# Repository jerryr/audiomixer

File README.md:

# audiomixer
Kicad project for audio mixer

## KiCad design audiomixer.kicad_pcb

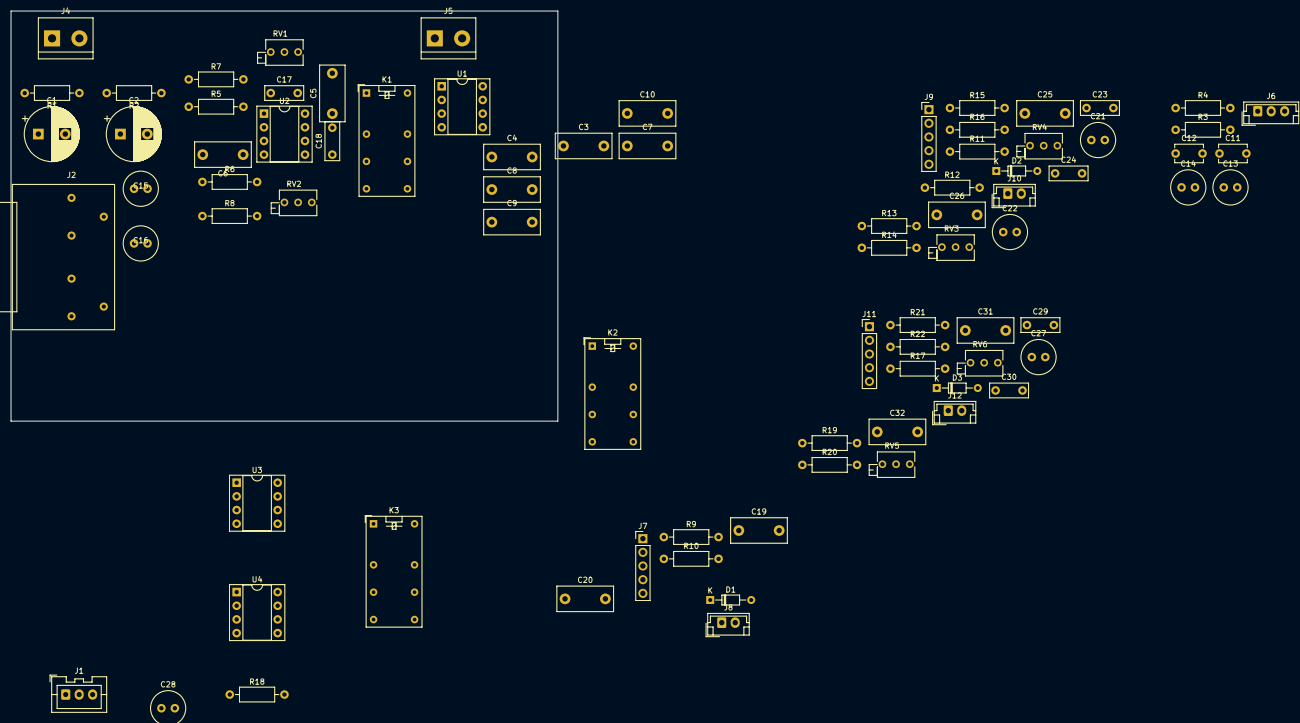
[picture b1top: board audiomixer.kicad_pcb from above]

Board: 2 copper layers, 101.6 x 76.2 mm, 81 parts (0 on the bottom side), 62 nets, no tracks yet.

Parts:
C1, C2: 1000uF; CP_Radial_D10.0mm_P5.00mm
C3, C4, C5, C6, C7, C8, C9, C10: 100n; C_Rect_L10.3mm_W4.5mm_P7.50mm_MKS4
C11, C12: 22p; C_Disc_D5.1mm_W3.2mm_P5.00mm
C13, C14: 22u; C_Radial_D6.3mm_H11.0mm_P2.50mm
C15, C16, C21, C22, C27, C28: 10u; C_Radial_D6.3mm_H11.0mm_P2.50mm
C17, C18, C23, C24, C29, C30: 47p; C_Rect_L7.0mm_W2.5mm_P5.00mm
C19, C20, C25, C26, C31, C32: 10u; C_Rect_L10.3mm_W4.5mm_P7.50mm_MKS4
D1, D2, D3: DIODE; D_DO-34_SOD68_P7.62mm_Horizontal
J1: Channel 3 In; JST_XA_B03B-XASK-1_1x03_P2.50mm_Vertical
J2: Dual_Stereo_RCA_Jack; Dual Stereo RCA Jack
J4: Power Input 24V; TerminalBlock_bornier-2_P5.08mm
J5: Power Input 5v; TerminalBlock_bornier-2_P5.08mm
J6: Conn_01x03_Male; JST_EH_B3B-EH-A_1x03_P2.50mm_Vertical
J7, J9, J11: Volume Control; PinHeader_1x05_P2.54mm_Vertical
J8, J10, J12: Muting Control; JST_EH_B2B-EH-A_1x02_P2.50mm_Vertical
K1, K2, K3: EC2-5NU; Relay_DPDT_Omron_G5V-2
R1, R2: 10K; R_Axial_DIN0207_L6.3mm_D2.5mm_P10.16mm_Horizontal
R3, R4, R7, R8, R9, R10, R13, R14, R15, R16, R19, R20, R21, R22: 22K; R_Axial_DIN0207_L6.3mm_D2.5mm_P10.16mm_Horizontal
R5, R6, R11, R12, R17, R18: 47K; R_Axial_DIN0207_L6.3mm_D2.5mm_P10.16mm_Horizontal
RV1, RV2, RV3, RV4, RV5, RV6: 100K; Potentiometer_Bourns_3266Z_Horizontal
U1, U2, U3, U4: TL072; DIP-8_W7.62mm_Socket

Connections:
+5V: J5.1, J8.1, J10.1, J12.1
/Channel 1/L In: C15.1, J2.2 (Left)
/Channel 1/L Out: C11.1, R3.1, R9.2, R15.2, R21.2, U1.2 (-)
/Channel 1/R In: C16.1, J2.1 (Right)
/Channel 1/R Out: C12.1, R4.1, R10.2, R16.2, R22.2, U1.5 (+)
/Channel 2/L In: C21.1, J2.5 (Left)
/Channel 2/R In: C22.1, J2.4 (Right)
/Channel 3/L In: C27.1, J1.3
/Channel 3/R In: C28.1, J1.1
GND: C1.2, C2.1, C3.2, C4.2, C5.2, C6.2, C7.2, C8.2, C9.2, C10.2, J1.2, J2.3 (Common), J2.6 (Common), J7.3, J9.3, J11.3, K1.6, K1.11, K2.6, K2.11, K3.6, K3.11, R1.1, R2.2, U1.3 (+), U1.6 (-), U2.3 (+), U2.5 (+), U3.3 (+), U3.5 (+), U4.3 (+), U4.5 (+)
GND2: D1.1 (K), D2.1 (K), D3.1 (K), J5.2, K1.16, K2.16, K3.16
unnamed: C11.2, C13.1, R3.2, U1.1
unnamed: C12.2, C14.1, R4.2, U1.7
unnamed: C13.2, J6.3
unnamed: C14.2, J6.1
unnamed: C15.2, R5.1
unnamed: C16.2, R6.1
unnamed: C17.1, R5.2, R7.1, U2.2 (-)
unnamed: C17.2, C19.1, RV1.2, U2.1
unnamed: C18.1, R6.2, R8.1, U2.6 (-)
unnamed: C18.2, C20.1, RV2.2, U2.7
unnamed: C19.2, J7.1
unnamed: C20.2, J7.5
unnamed: C21.2, R11.1
unnamed: C22.2, R12.1
unnamed: C23.1, R11.2, R13.1, U3.2 (-)
unnamed: C23.2, C25.1, RV3.2, U3.1
unnamed: C24.1, R12.2, R14.1, U3.6 (-)
unnamed: C24.2, C26.1, RV4.2, U3.7
unnamed: C25.2, J9.1
unnamed: C26.2, J9.5
unnamed: C27.2, R17.1
unnamed: C28.2, R18.1
unnamed: C29.1, R17.2, R19.1, U4.2 (-)
unnamed: C29.2, C31.1, RV5.2, U4.1
unnamed: C30.1, R18.2, R20.1, U4.6 (-)
unnamed: C30.2, C32.1, RV6.2, U4.7
unnamed: C31.2, J11.1
unnamed: C32.2, J11.5
unnamed: D1.2 (A), J8.2, K1.1
unnamed: D2.2 (A), J10.2, K2.1
unnamed: D3.2 (A), J12.2, K3.1
unnamed: J7.2, K1.4
unnamed: J7.4, K1.13
unnamed: J9.2, K2.4
unnamed: J9.4, K2.13
unnamed: J11.2, K3.4
unnamed: J11.4, K3.13
unnamed: K1.8, R9.1
unnamed: K1.9, R10.1
unnamed: K2.8, R15.1
unnamed: K2.9, R16.1
unnamed: K3.8, R21.1
unnamed: K3.9, R22.1
unnamed: R7.2, RV1.1
unnamed: R8.2, RV2.1
unnamed: R13.2, RV3.1
unnamed: R14.2, RV4.1
unnamed: R19.2, RV5.1
unnamed: R20.2, RV6.1
VCC: C1.1, C3.1, C5.1, C7.1, C9.1, J4.1, R1.2, U1.8 (V+), U2.8 (V+), U3.8 (V+), U4.8 (V+)
VDD: C2.2, C4.1, C6.1, C8.1, C10.1, J4.2, J6.2, R2.1, U1.4 (V-), U2.4 (V-), U3.4 (V-), U4.4 (V-)

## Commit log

2022-09-19 added schematic
2022-09-19 added power schematic
2022-09-19 Added decoupling and output caps
2022-10-23 Refactored and made modular inputs
2022-10-23 Update footprints
2022-11-17 Finalize schematic and start with PCB layout
